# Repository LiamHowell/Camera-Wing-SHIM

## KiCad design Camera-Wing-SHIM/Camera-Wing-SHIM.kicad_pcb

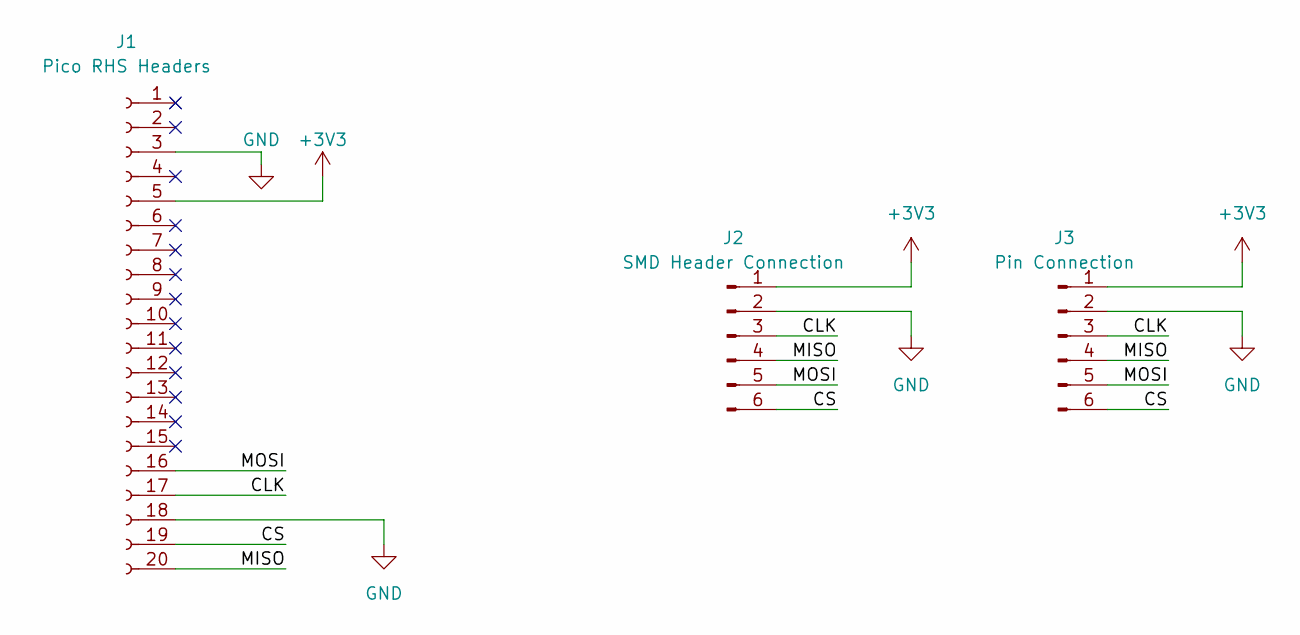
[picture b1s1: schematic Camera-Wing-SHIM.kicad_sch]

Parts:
J1: Pico RHS Headers; Pico-Wing-Shim-SPI
J2: SMD Header Connection; 6-pin-SMD-R2
J3: Pin Connection; PinHeader_1x06_P2.54mm_Vertical

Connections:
+3V3: J1.5, J2.1, J3.1
/CLK: J1.17, J2.3, J3.3
/CS: J1.19, J2.6, J3.6
/MISO: J1.20, J2.4, J3.4
/MOSI: J1.16, J2.5, J3.5
GND: J1.3, J1.18, J2.2, J3.2

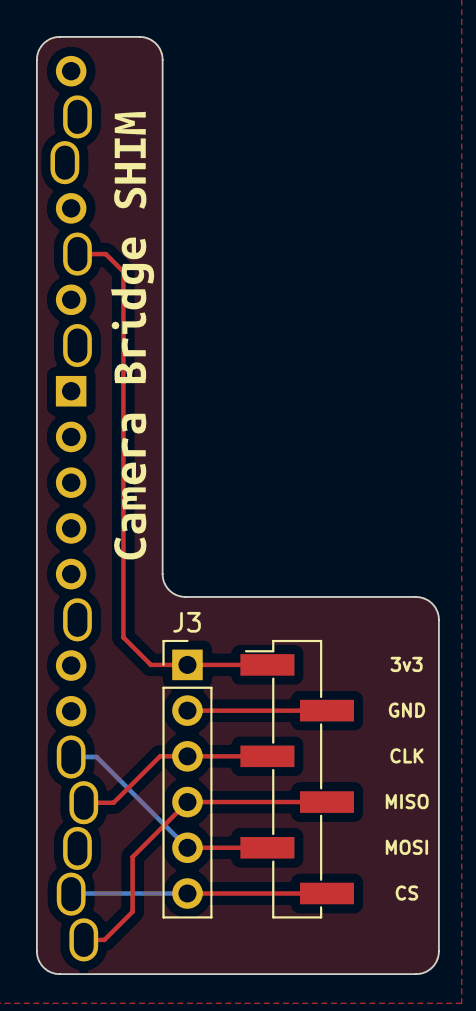
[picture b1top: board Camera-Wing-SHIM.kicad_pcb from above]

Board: 2 copper layers, 22.3 x 52.1 mm, 4 parts (0 on the bottom side), 6 nets.

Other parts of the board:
kibuzzard-65ACBA76: G***; kibuzzard-65ACBA76

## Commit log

2023-12-11 Made PCB
2024-01-21 Moved to SMD header
2024-02-02 Fixed
